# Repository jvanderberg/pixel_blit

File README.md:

# pixel_blit

A 32-channel addressable LED controller based on the Raspberry Pi RP2350B microcontroller.

<details>
<summary>Top view</summary>

</details>

> **Status:** the images show v4.0. This branch (`v5`) is the next revision:
> Wi-Fi instead of LVDS, four independent 5-24 V power zones, a new power
> supply and an on-board status LED and button. It is designed but not yet
> built; bring-up and firmware come after prototyping the RM2 module and
> receiving boards. Design notes, part choices and as-built values are in
> [docs/next-revision.md](docs/next-revision.md).

## Overview

The pixel_blit drives up to 32 strings of addressable LEDs from one board. The
outputs are split into four power zones, each with its own supply input, so
5 V, 12 V and 24 V pixels can run from the same controller. Shows play from a
microSD card; the board is set up and controlled over Wi-Fi, USB or an IR
remote.

## Key Specifications

- **Microcontroller**: Raspberry Pi RP2350B (QFN-80)
  - Dual Cortex-M33 cores @ 150 MHz
  - 12 PIO state machines for LED timing
  - USB Full Speed (12 Mbps)

- **Output Channels**: 32 independent LED string outputs
  - 3.3 V to 5 V level shifting (4× SN74LVC8T245)
  - 47 Ω series resistor on every data line
  - 3 A / 30 V resettable fuse (PTC) on every port
  - Screw terminals (3.5 mm pitch): power, data, ground

- **Power Zones**: 4 zones of 8 outputs each
  - One input per zone, **5-24 V DC**
  - 20 A blade fuse, reverse-polarity ideal diode (LM74700 + 60 V FET) and 26 V TVS on each input
  - A blown-fuse LED beside each fuse
  - Silkscreen key with a write-in voltage box per zone

- **Memory**:
  - 16 MB QSPI flash (W25Q128JV)
  - 8 MB QSPI PSRAM (APS6404L), on the flash bus
  - microSD card slot for shows and settings

- **Wireless**: Raspberry Pi RM2 module (CYW43439, 2.4 GHz Wi-Fi and Bluetooth)

- **User Interface**:
  - Common-cathode RGB status LED
  - Play button, plus Boot and Reset buttons
  - IR receiver jack with a polarity switch
  - USB-C

## Power

```
Zone inputs 1-4 (5-24 V each)
  → 20 A blade fuse → LM74700 ideal diode (blocks a reversed supply) → zone rail VZ1-VZ4
       (SMBJ26A TVS on the rail) → 8 ports, each through a 3 A PTC
  → SS34 diodes (OR of all four zones) → VIN_SYS
       → TPS552872 buck-boost (4.5-28 V in) → 5.2 V → B5819W → +5 V (level shifters)
       → TPS62A02A buck → 3.3 V (MCU, flash, PSRAM, Wi-Fi, SD)
       → RP2350B internal regulator → 1.1 V core
```

The logic supply runs from whichever zones are powered, so any one input is
enough to run the board. USB can power the logic alone. A 4-pin header (3.3 V,
5 V, VIN, GND) allows external supplies; see the notes on the schematic before
using it.

## Signal Path

```
RP2350B GPIO (3.3 V)
  → SN74LVC8T245 level shifter (4× 8-channel)
  → 47 Ω series resistor
  → screw terminal
  → LED string
```

24 V pixels still take 5 V logic data.

## Pin Map

| GPIO | Function |
|---|---|
| 0-31 | LED strings (firmware maps string numbers to GPIOs) |
| 32-35 | RM2 Wi-Fi (power, chip select, data, clock) |
| 36-39 | microSD (SPI) |
| 40 | Play button (to GND, internal pull-up) |
| 41, 43, 45 | Status LED blue, red, green |
| 42 | IR receiver |
| 44, 46 | Spare |
| 47 | PSRAM chip select (XIP_CS1) |

Strings are numbered by zone on the silkscreen: zone 1 is S0-S7, zone 2 S8-S15,
zone 3 S16-S23, zone 4 S24-S31.

## Board Details

- **PCB size**: 197.5 mm × 122.1 mm
- **Layers**: 4 (signal / GND / GND with a local 3.3 V area / signal and GND)
- **Assembly**: all parts on the top side
- **Connectors**:
  - 32× DB301V 3.5 mm screw terminals (LED outputs)
  - 4× DBT50G 9.5 mm screw terminals (zone power inputs)
  - 4× XF-507P blade fuse holders
  - USB-C, microSD, IR jack, SWD header, power override header

## Component Summary

| Type | Count | Notes |
|------|-------|-------|
| Resistors | 67 | 47 Ω series resistors, regulator feedback, LED resistors |
| Capacitors | 61 | Decoupling, regulator input and output, ideal-diode charge pumps |
| Fuses | 36 | 32 port PTCs, 4 blade fuse holders |
| ICs and modules | 14 | MCU, flash, PSRAM, RM2, 4 level shifters, 2 regulators, 4 ideal-diode controllers |
| MOSFETs | 4 | BSC014N06NS, one per zone input (ideal diode) |
| Diodes and LEDs | 52 | 32 data-line TVS, zone TVS, OR diodes, IR clamp, USB protection, status and fuse LEDs |
| Terminal blocks | 36 | 32 LED outputs, 4 zone inputs |
| Buttons and switches | 4 | Play, Boot, Reset, IR polarity |

## File Structure

```
pixel_blit/
├── pixel_blit.kicad_pcb      # PCB layout
├── pixel_blit.kicad_sch      # Top-level schematic: MCU, flash, PSRAM, USB, status LED, buttons
├── Power.kicad_sch           # Zone inputs and ideal diodes, buck-boost, 3.3 V buck, fuse LEDs
├── output.kicad_sch          # Level shifters, series resistors, PTCs, terminals
├── wireless.kicad_sch        # RM2 Wi-Fi module
├── peripherals.kicad_sch     # microSD, IR receiver
├── PixelBlit.kicad_sym/.pretty, JLCImport.kicad_sym/.pretty  # Project libraries
├── docs/                     # Design notes (next-revision.md) and images
└── production/               # Manufacturing outputs
```

## Use Cases

- Architectural lighting installations
- Stage and entertainment lighting
- Large-scale pixel displays
- Holiday and decorative lighting
- Interactive art installations

## License

MIT License

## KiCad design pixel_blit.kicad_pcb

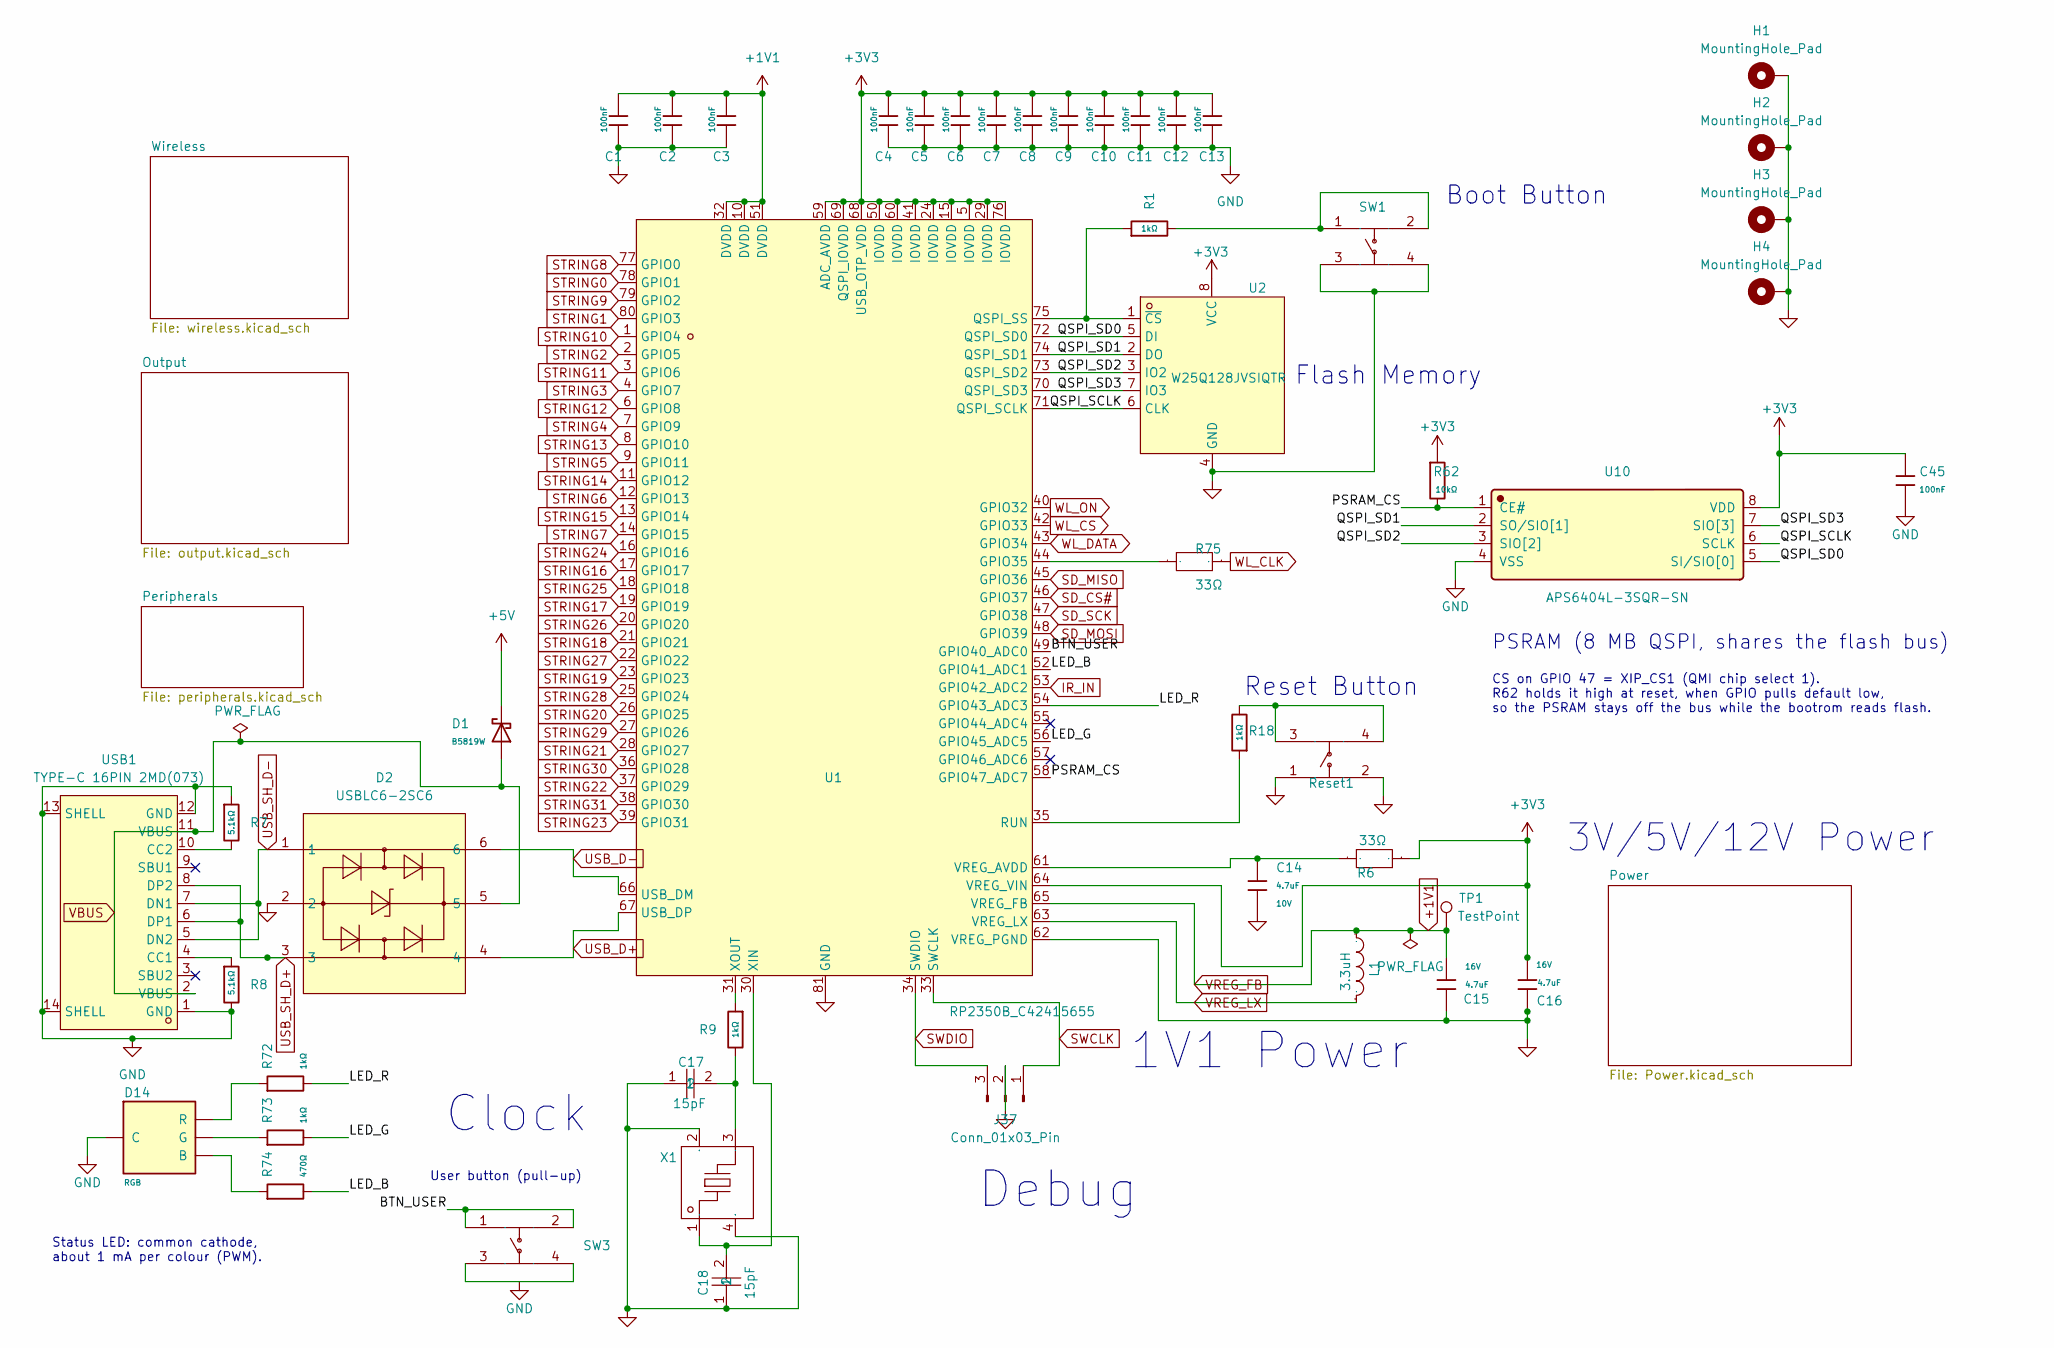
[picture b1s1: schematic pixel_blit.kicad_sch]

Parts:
C1, C2, C3, C4, C5, C6, C7, C8, C9, C10, C11, C12, C13, C45: 100nF; C_0402; Voltage Rated 16V; Tolerance ±10%; Part CL05B104KO5NNNC; LCSC C1525
C14: 4.7uF; C_0402; Voltage Rated 10V; Tolerance ±20%; Part CL05A475MP5NRNC; LCSC C23733
C15, C16: 4.7uF; C_0603; Voltage Rated 16V; Tolerance ±10%; Part CL10A475KO8NNNC; LCSC C19666
C17, C18: 15pF; C0402; Manufacturer Part 0402CG150J500NT; LCSC Part Name 15pF ±5% 50V
D1: B5819W; D_SOD-123; Forward Voltage (Vf@If) 900mV@3A; Reverse Voltage (Vr) 40V; Part B5819W; LCSC C64885
D2: USBLC6-2SC6; SOT-23-6_L2.9-W1.6-P0.95-LS2.8-BL; LCSC Part C7519
D14: RGB; TJ-S1615CY6TGLCCSRGB-A5; Manufacturer Part TJ-S1615CY6TGLCCSRGB-A5; LCSC C601684
H1, H2, H3, H4: MountingHole_Pad; MountingHole_3.2mm_M3_Pad_Via
J37: Conn_01x03_Pin; PinHeader_1x03_P2.54mm_Vertical
L1: IND-SMD_L2.0-W1.6_AOTA-B201610S3R3-101-T; Manufacturer Part AOTA-B201610S3R3-101-T; LCSC Part Name AOTA-B201610S3R3-101-T
R1, R18, R72, R73: 1kΩ; R_0402; Overload Voltage (Max) 50V; Tolerance ±1%; Part 0402WGF1001TCE; LCSC C11702
R6, R75: 33Ω; R0402; Manufacturer Part 0402WGF330JTCE; LCSC Part Name 33Ω ±1% 62.5mW 厚膜电阻
R7, R8: 5.1kΩ; R_0402; Overload Voltage (Max) 50V; Tolerance ±1%; Part 0402WGF5101TCE; LCSC C25905
R9: 1kΩ; R_0603; Overload Voltage (Max) 75V; Tolerance ±1%; Part 0603WAF1001T5E; LCSC C21190
R62: 10kΩ; R_0402; Overload Voltage (Max) 50V; Tolerance ±1%; Part 0402WGF1002TCE; LCSC C25744
R74: 470Ω; R_0402; Overload Voltage (Max) 50V; Tolerance ±1%; Part 0402WGF4700TCE; LCSC C25117
Reset1: K2-1808SN-A4SW-01; KEY-SMD_4P-L4.2-W3.2-P2.20-LS5.1-TL; Manufacturer Part K2-1808SN-A4SW-01; LCSC Part Name 4.2mm*3.25mm
SW1: K2-1808SN-A4SW; KEY-SMD_4P-L4.2-W3.2-P2.20-LS5.1-TL; LCSC Part C92589
SW3: KEY-SMD_4P-L4.2-W3.2-P2.20-LS5.1-TL; Manufacturer Part K2-1808SN-A4SW-01; LCSC Part Name 4.2mm*3.25mm
TP1: TestPoint; TestPoint_Pad_1.0x1.0mm
U1: RP2350B_C42415655; QFN-80_L10.0-W10.0-P0.40-TL-EP3.4; LCSC Part C42415655
U2: W25Q128JVSIQTR; SOIC-8_L5.3-W5.3-P1.27-LS8.0-BL; LCSC Part C97521
U10: APS6404L-3SQR-SN; APS6404L-3SQR-SN_C5333729; Manufacturer Part APS6404L-3SQR-SN; LCSC C5333729
USB1: TYPE-C 16PIN 2MD(073); USB-C-SMD_TYPE-C-6PIN-2MD-073; LCSC Part C2765186
X1: CRYSTAL-SMD_4P-L3.2-W2.5-BL; Manufacturer Part ABM8-272-T3; LCSC Part Name ABM8-272-T3

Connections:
+1V1: C1.1, C2.1, C3.1, C15.2, L1.2, TP1.1, U1.10 (DVDD), U1.32 (DVDD), U1.51 (DVDD), U1.65 (VREG_FB)
+3V3: C4.1, C5.1, C6.1, C7.1, C8.1, C9.1, C10.1, C11.1, C12.1, C13.1, C16.2, C45.1, R6.1, R62.1, U1.5 (IOVDD), U1.15 (IOVDD), U1.24 (IOVDD), U1.29 (IOVDD), U1.41 (IOVDD), U1.50 (IOVDD), U1.59 (ADC_AVDD), U1.60 (IOVDD), U1.64 (VREG_VIN), U1.68 (USB_OTP_VDD), U1.69 (QSPI_IOVDD), U1.76 (IOVDD), U2.8 (VCC), U10.8 (VDD); also elsewhere on the board
+5V: D1.1; also elsewhere on the board
/BTN_USER: SW3.1, SW3.2, U1.49 (GPIO40_ADC0)
/LED_B: R74.2, U1.52 (GPIO41_ADC1)
/LED_G: R73.2, U1.56 (GPIO45_ADC5)
/LED_R: R72.2, U1.54 (GPIO43_ADC3)
/PSRAM_CS: R62.2, U1.58 (GPIO47_ADC7), U10.1 (CE#)
/QSPI_SCLK: U1.71 (QSPI_SCLK), U2.6 (CLK), U10.6 (SCLK)
/QSPI_SD0: U1.72 (QSPI_SD0), U2.5 (DI), U10.5 (SI/SIO[0])
/QSPI_SD1: U1.74 (QSPI_SD1), U2.2 (DO), U10.2 (SO/SIO[1])
/QSPI_SD2: U1.73 (QSPI_SD2), U2.3 (IO2), U10.3 (SIO[2])
/QSPI_SD3: U1.70 (QSPI_SD3), U2.7 (IO3), U10.7 (SIO[3])
GND: C1.2, C2.2, C3.2, C4.2, C5.2, C6.2, C7.2, C8.2, C9.2, C10.2, C11.2, C12.2, C13.2, C14.2, C15.1, C16.1, C17.1, C18.1, C45.2, D2.2, D14.1 (C), H1.1, H2.1, H3.1, H4.1, J37.2, R7.1, R8.2, Reset1.1, Reset1.2, SW1.3, SW1.4, SW3.3, SW3.4, U1.62 (VREG_PGND), U1.81 (GND), U2.4 (GND), U10.4 (VSS), USB1.1 (GND), USB1.12 (GND), USB1.13 (SHELL), USB1.14 (SHELL), X1.2 (GND), X1.4 (GND); also elsewhere on the board
IR_IN: U1.53 (GPIO42_ADC2); also elsewhere on the board
unnamed: C17.2, R9.2, X1.3
unnamed: D14.2 (B), R74.1
unnamed: D14.3 (G), R73.1
unnamed: D14.4 (R), R72.1
unnamed: R1.2, SW1.1, SW1.2
unnamed: R18.2, Reset1.3, Reset1.4
unnamed: R75.2, U1.44 (GPIO35)
unnamed: R1.1, U1.75 (QSPI_SS), U2.1 (~CS)
unnamed: R18.1, U1.35 (RUN)
unnamed: C14.1, R6.2, U1.61 (VREG_AVDD)
unnamed: C18.2, U1.30 (XIN), X1.1
unnamed: R9.1, U1.31 (XOUT)
unnamed: R8.1, USB1.4 (CC1)
unnamed: R7.2, USB1.10 (CC2)
SD_CS#: U1.46 (GPIO37); also elsewhere on the board
SD_MISO: U1.45 (GPIO36); also elsewhere on the board
SD_MOSI: U1.48 (GPIO39); also elsewhere on the board
SD_SCK: U1.47 (GPIO38); also elsewhere on the board
STRING0: U1.78 (GPIO1); also elsewhere on the board
STRING1: U1.80 (GPIO3); also elsewhere on the board
STRING2: U1.2 (GPIO5); also elsewhere on the board
STRING3: U1.4 (GPIO7); also elsewhere on the board
STRING4: U1.7 (GPIO9); also elsewhere on the board
STRING5: U1.9 (GPIO11); also elsewhere on the board
STRING6: U1.12 (GPIO13); also elsewhere on the board
STRING7: U1.14 (GPIO15); also elsewhere on the board
STRING8: U1.77 (GPIO0); also elsewhere on the board
STRING9: U1.79 (GPIO2); also elsewhere on the board
STRING10: U1.1 (GPIO4); also elsewhere on the board
STRING11: U1.3 (GPIO6); also elsewhere on the board
STRING12: U1.6 (GPIO8); also elsewhere on the board
STRING13: U1.8 (GPIO10); also elsewhere on the board
STRING14: U1.11 (GPIO12); also elsewhere on the board
STRING15: U1.13 (GPIO14); also elsewhere on the board
STRING16: U1.17 (GPIO17); also elsewhere on the board
STRING17: U1.19 (GPIO19); also elsewhere on the board
STRING18: U1.21 (GPIO21); also elsewhere on the board
STRING19: U1.23 (GPIO23); also elsewhere on the board
STRING20: U1.26 (GPIO25); also elsewhere on the board
STRING21: U1.28 (GPIO27); also elsewhere on the board
STRING22: U1.37 (GPIO29); also elsewhere on the board
STRING23: U1.39 (GPIO31); also elsewhere on the board
STRING24: U1.16 (GPIO16); also elsewhere on the board
STRING25: U1.18 (GPIO18); also elsewhere on the board
STRING26: U1.20 (GPIO20); also elsewhere on the board
STRING27: U1.22 (GPIO22); also elsewhere on the board
STRING28: U1.25 (GPIO24); also elsewhere on the board
STRING29: U1.27 (GPIO26); also elsewhere on the board
STRING30: U1.36 (GPIO28); also elsewhere on the board
STRING31: U1.38 (GPIO30); also elsewhere on the board
SWCLK: J37.1, U1.33 (SWCLK)
SWDIO: J37.3, U1.34 (SWDIO)
USB_D+: D2.4, U1.67 (USB_DP)
USB_D-: D2.6, U1.66 (USB_DM)
USB_SH_D+: D2.3, USB1.6 (DP1), USB1.8 (DP2)
USB_SH_D-: D2.1, USB1.5 (DN2), USB1.7 (DN1)
VBUS: D1.2, D2.5, USB1.2 (VBUS), USB1.11 (VBUS)
VREG_LX: L1.1, U1.63 (VREG_LX)
WL_CLK: R75.1; also elsewhere on the board
WL_CS: U1.42 (GPIO33); also elsewhere on the board
WL_DATA: U1.43 (GPIO34); also elsewhere on the board
WL_ON: U1.40 (GPIO32); also elsewhere on the board

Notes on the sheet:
Reset Button
Debug
Status LED: common cathode, about 1 mA per colour (PWM).
Boot Button
Clock
CS on GPIO 47 = XIP_CS1 (QMI chip select 1). R62 holds it high at reset, when GPIO pulls default low, so the PSRAM stays off the bus while the bootrom reads flash.
3V/5V/12V Power
Flash Memory
PSRAM (8 MB QSPI, shares the flash bus)
User button (pull-up)
1V1 Power

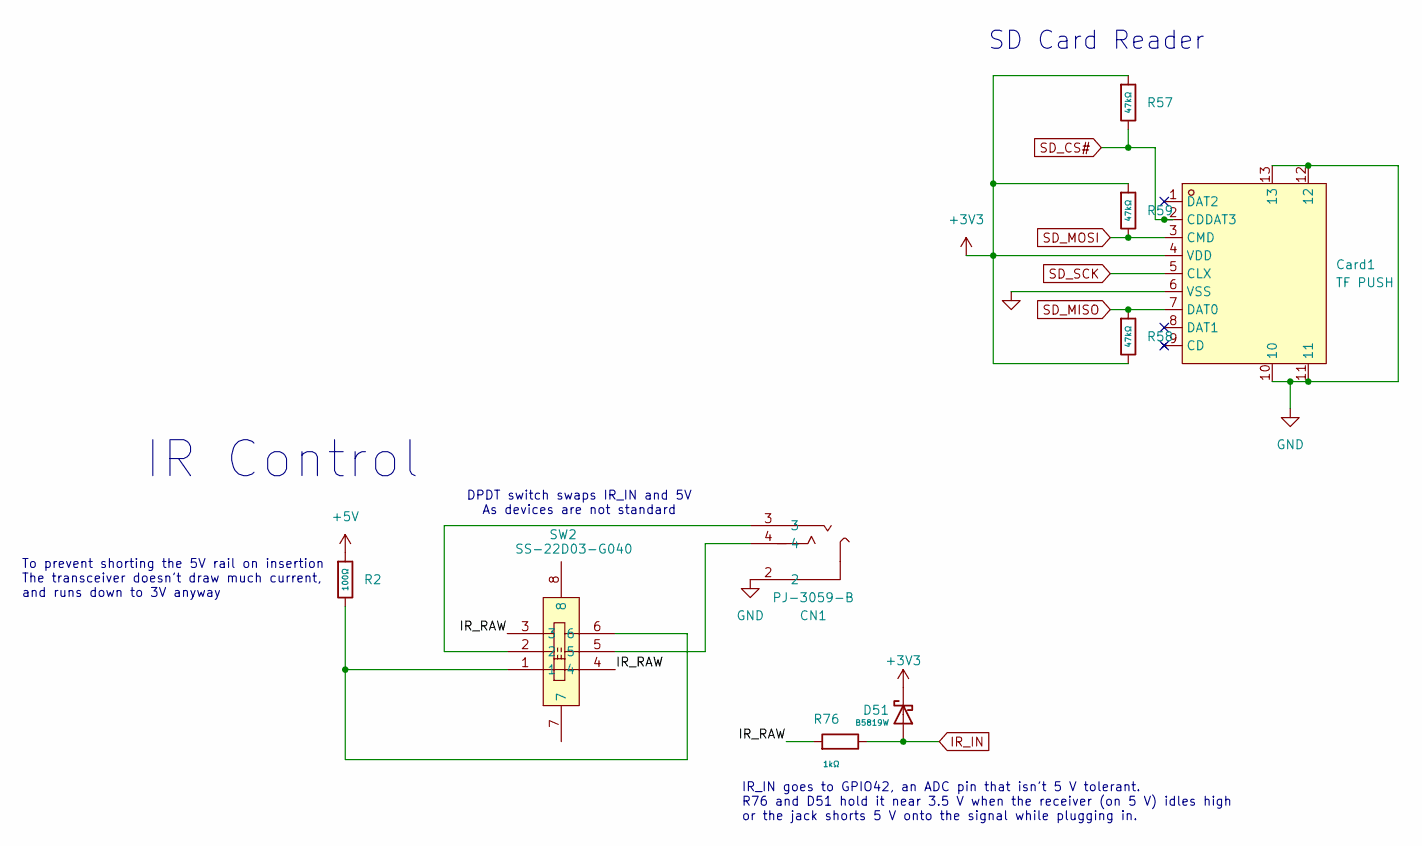
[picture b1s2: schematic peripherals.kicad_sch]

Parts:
CN1: PJ-3059-B; AUDIO-TH_XKB_PJ-3059-B; LCSC Part C2884976
Card1: TF PUSH; TF-SMD_TF-PUSH; LCSC Part C393941
D51: B5819W; D_SOD-123; Forward Voltage (Vf@If) 900mV@3A; Reverse Voltage (Vr) 40V; Part B5819W; LCSC C64885
R2: 100Ω; R_0603; Overload Voltage (Max) 75V; Tolerance ±1%; Part 0603WAF1000T5E; LCSC C22775
R57, R58, R59: 47kΩ; R_0402; Overload Voltage (Max) 50V; Tolerance ±1%; Part 0402WGF4702TCE; LCSC C25792
R76: 1kΩ; R_0402; Overload Voltage (Max) 50V; Tolerance ±1%; Part 0402WGF1001TCE; LCSC C11702
SW2: SS-22D03-G040; SW-TH_SS-22D03-G4; LCSC Part C2848923

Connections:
+3V3: Card1.4 (VDD), D51.1, R57.1, R58.2, R59.1; also elsewhere on the board
+5V: R2.1; also elsewhere on the board
/Peripherals/IR_RAW: R76.1, SW2.3, SW2.4
GND: CN1.2, Card1.6 (VSS), Card1.10, Card1.11, Card1.12, Card1.13; also elsewhere on the board
IR_IN: D51.2, R76.2; also elsewhere on the board
unnamed: CN1.3, SW2.2
unnamed: CN1.4, SW2.5
unnamed: R2.2, SW2.1, SW2.6
SD_CS#: Card1.2 (CDDAT3), R57.2; also elsewhere on the board
SD_MISO: Card1.7 (DAT0), R58.1; also elsewhere on the board
SD_MOSI: Card1.3 (CMD), R59.2; also elsewhere on the board
SD_SCK: Card1.5 (CLX); also elsewhere on the board

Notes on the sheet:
IR Control
SD Card Reader
DPDT switch swaps IR_IN and 5V As devices are not standard
To prevent shorting the 5V rail on insertion The transceiver doesn't draw much current, and runs down to 3V anyway
IR_IN goes to GPIO42, an ADC pin that isn't 5 V tolerant. R76 and D51 hold it near 3.5 V when the receiver (on 5 V) idles high or the jack shorts 5 V onto the signal while plugging in.

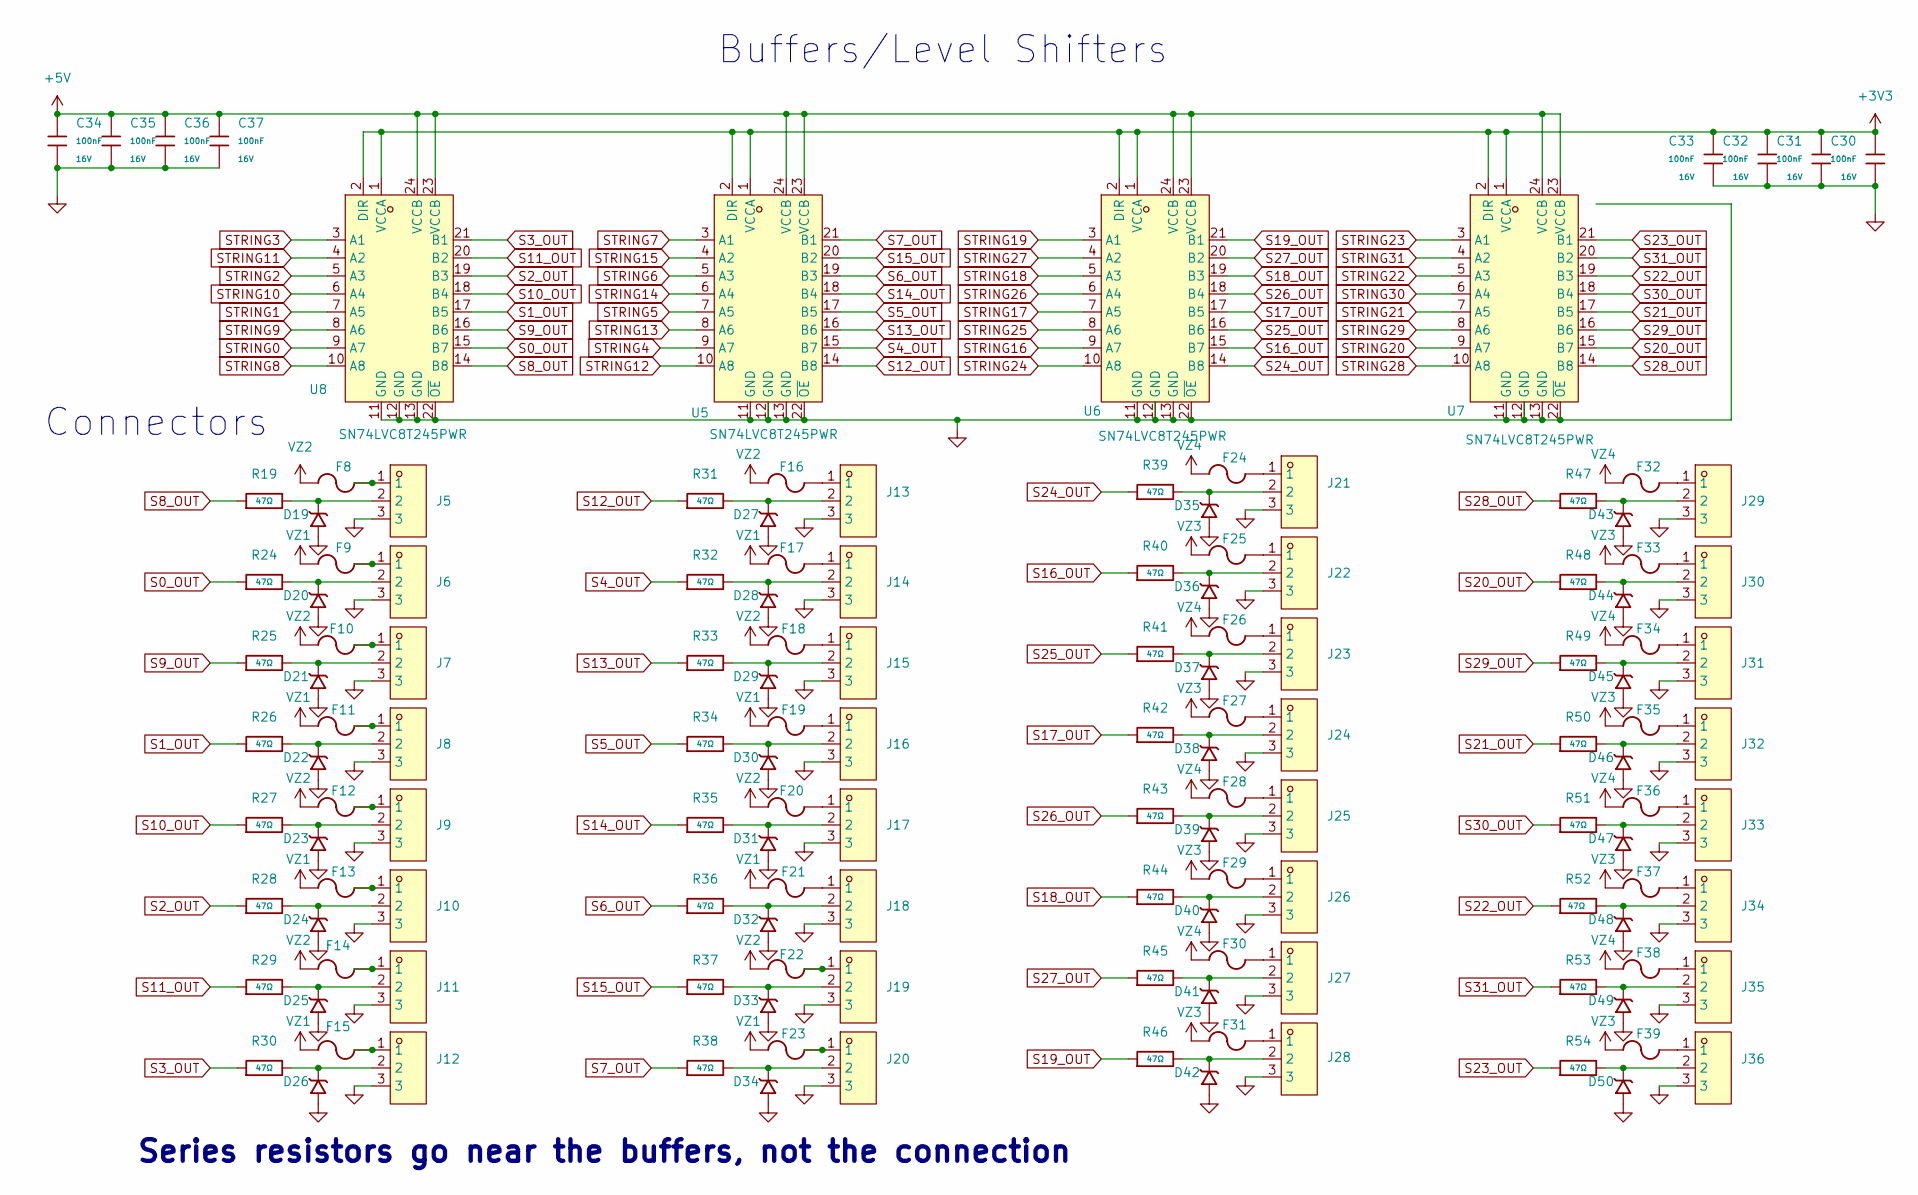
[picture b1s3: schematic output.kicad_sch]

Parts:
C30, C31, C32, C33, C34, C35, C36, C37: 100nF; C_0402; Voltage Rated 16V; Tolerance ±10%; Part CL05B104KO5NNNC; LCSC C1525
D19, D20, D21, D22, D23, D24, D25, D26, D27, D28, D29, D30, D31, D32, D33, D34, D35, D36, D37, D38, D39, D40, D41, D42, D43, D44, D45, D46, D47, D48, D49, D50: SMF5.0A; SMF5_0A_C193402; Manufacturer Part SMF5.0A; LCSC C193402
F8, F9, F10, F11, F12, F13, F14, F15, F16, F17, F18, F19, F20, F21, F22, F23, F24, F25, F26, F27, F28, F29, F30, F31, F32, F33, F34, F35, F36, F37, F38, F39: 1812L300/30GR; 1812L300_30GR; Manufacturer Part 1812L300/30GR; LCSC C48985875
J5, J6, J7, J8, J9, J10, J11, J12, J13, J14, J15, J16, J17, J18, J19, J20, J21, J22, J23, J24, J25, J26, J27, J28, J29, J30, J31, J32, J33, J34, J35, J36: DB301V-3.5-3P-GN; CONN-TH_DB301V-3.5-3P-GN; LCSC Part C695630
R19, R24, R25, R26, R27, R28, R29, R30, R31, R32, R33, R34, R35, R36, R37, R38, R39, R40, R41, R42, R43, R44, R45, R46, R47, R48, R49, R50, R51, R52, R53, R54: 47Ω; R_0402; Overload Voltage (Max) 50V; Tolerance ±1%; Part 0402WGF470JTCE; LCSC C25118
U5, U6, U7, U8: SN74LVC8T245PWR; TSSOP-24_L7.8-W4.4-P0.65-LS6.4-BL; LCSC Part C27643

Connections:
+3V3: C30.1, C31.1, C32.1, C33.1, U5.1 (VCCA), U5.2 (DIR), U6.1 (VCCA), U6.2 (DIR), U7.1 (VCCA), U7.2 (DIR), U8.1 (VCCA), U8.2 (DIR); also elsewhere on the board
+5V: C34.1, C35.1, C36.1, C37.1, U5.23 (VCCB), U5.24 (VCCB), U6.23 (VCCB), U6.24 (VCCB), U7.23 (VCCB), U7.24 (VCCB), U8.23 (VCCB), U8.24 (VCCB); also elsewhere on the board
GND: C30.2, C31.2, C32.2, C33.2, C34.2, C35.2, C36.2, C37.2, D19.2 (A), D20.2 (A), D21.2 (A), D22.2 (A), D23.2 (A), D24.2 (A), D25.2 (A), D26.2 (A), D27.2 (A), D28.2 (A), D29.2 (A), D30.2 (A), D31.2 (A), D32.2 (A), D33.2 (A), D34.2 (A), D35.2 (A), D36.2 (A), D37.2 (A), D38.2 (A), D39.2 (A), D40.2 (A), D41.2 (A), D42.2 (A), D43.2 (A), D44.2 (A), D45.2 (A), D46.2 (A), D47.2 (A), D48.2 (A), D49.2 (A), D50.2 (A), J5.3, J6.3, J7.3, J8.3, J9.3, J10.3, J11.3, J12.3, J13.3, J14.3, J15.3, J16.3, J17.3, J18.3, J19.3, J20.3, J21.3, J22.3, J23.3, J24.3, J25.3, J26.3, J27.3, J28.3, J29.3, J30.3, J31.3, J32.3, J33.3, J34.3, J35.3, J36.3, U5.11 (GND), U5.12 (GND), U5.13 (GND), U5.22 (~OE), U6.11 (GND), U6.12 (GND), U6.13 (GND), U6.22 (~OE), U7.11 (GND), U7.12 (GND), U7.13 (GND), U7.22 (~OE), U8.11 (GND), U8.12 (GND), U8.13 (GND), U8.22 (~OE); also elsewhere on the board
unnamed: D19.1 (C), J5.2, R19.2
unnamed: D20.1 (C), J6.2, R24.2
unnamed: D21.1 (C), J7.2, R25.2
unnamed: D22.1 (C), J8.2, R26.2
unnamed: D23.1 (C), J9.2, R27.2
unnamed: D24.1 (C), J10.2, R28.2
unnamed: D25.1 (C), J11.2, R29.2
unnamed: D26.1 (C), J12.2, R30.2
unnamed: D27.1 (C), J13.2, R31.2
unnamed: D28.1 (C), J14.2, R32.2
unnamed: D29.1 (C), J15.2, R33.2
unnamed: D30.1 (C), J16.2, R34.2
unnamed: D31.1 (C), J17.2, R35.2
unnamed: D32.1 (C), J18.2, R36.2
unnamed: D33.1 (C), J19.2, R37.2
unnamed: D34.1 (C), J20.2, R38.2
unnamed: D35.1 (C), J21.2, R39.2
unnamed: D36.1 (C), J22.2, R40.2
unnamed: D37.1 (C), J23.2, R41.2
unnamed: D38.1 (C), J24.2, R42.2
unnamed: D39.1 (C), J25.2, R43.2
unnamed: D40.1 (C), J26.2, R44.2
unnamed: D41.1 (C), J27.2, R45.2
unnamed: D42.1 (C), J28.2, R46.2
unnamed: D43.1 (C), J29.2, R47.2
unnamed: D44.1 (C), J30.2, R48.2
unnamed: D45.1 (C), J31.2, R49.2
unnamed: D46.1 (C), J32.2, R50.2
unnamed: D47.1 (C), J33.2, R51.2
unnamed: D48.1 (C), J34.2, R52.2
unnamed: D49.1 (C), J35.2, R53.2
unnamed: D50.1 (C), J36.2, R54.2
unnamed: F8.2, J5.1
unnamed: F9.2, J6.1
unnamed: F10.2, J7.1
unnamed: F11.2, J8.1
unnamed: F12.2, J9.1
unnamed: F13.2, J10.1
unnamed: F14.2, J11.1
unnamed: F15.2, J12.1
unnamed: F16.2, J13.1
unnamed: F17.2, J14.1
unnamed: F18.2, J15.1
unnamed: F19.2, J16.1
unnamed: F20.2, J17.1
unnamed: F21.2, J18.1
unnamed: F22.2, J19.1
unnamed: F23.2, J20.1
unnamed: F24.2, J21.1
unnamed: F25.2, J22.1
unnamed: F26.2, J23.1
unnamed: F27.2, J24.1
unnamed: F28.2, J25.1
unnamed: F29.2, J26.1
unnamed: F30.2, J27.1
unnamed: F31.2, J28.1
unnamed: F32.2, J29.1
unnamed: F33.2, J30.1
unnamed: F34.2, J31.1
unnamed: F35.2, J32.1
unnamed: F36.2, J33.1
unnamed: F37.2, J34.1
unnamed: F38.2, J35.1
unnamed: F39.2, J36.1
S0_OUT: R24.1, U8.15 (B7)
S1_OUT: R26.1, U8.17 (B5)
S2_OUT: R28.1, U8.19 (B3)
S3_OUT: R30.1, U8.21 (B1)
S4_OUT: R32.1, U5.15 (B7)
S5_OUT: R34.1, U5.17 (B5)
S6_OUT: R36.1, U5.19 (B3)
S7_OUT: R38.1, U5.21 (B1)
S8_OUT: R19.1, U8.14 (B8)
S9_OUT: R25.1, U8.16 (B6)
S10_OUT: R27.1, U8.18 (B4)
S11_OUT: R29.1, U8.20 (B2)
S12_OUT: R31.1, U5.14 (B8)
S13_OUT: R33.1, U5.16 (B6)
S14_OUT: R35.1, U5.18 (B4)
S15_OUT: R37.1, U5.20 (B2)
S16_OUT: R40.1, U6.15 (B7)
S17_OUT: R42.1, U6.17 (B5)
S18_OUT: R44.1, U6.19 (B3)
S19_OUT: R46.1, U6.21 (B1)
S20_OUT: R48.1, U7.15 (B7)
S21_OUT: R50.1, U7.17 (B5)
S22_OUT: R52.1, U7.19 (B3)
S23_OUT: R54.1, U7.21 (B1)
S24_OUT: R39.1, U6.14 (B8)
S25_OUT: R41.1, U6.16 (B6)
S26_OUT: R43.1, U6.18 (B4)
S27_OUT: R45.1, U6.20 (B2)
S28_OUT: R47.1, U7.14 (B8)
S29_OUT: R49.1, U7.16 (B6)
S30_OUT: R51.1, U7.18 (B4)
S31_OUT: R53.1, U7.20 (B2)
STRING0: U8.9 (A7); also elsewhere on the board
STRING1: U8.7 (A5); also elsewhere on the board
STRING2: U8.5 (A3); also elsewhere on the board
STRING3: U8.3 (A1); also elsewhere on the board
STRING4: U5.9 (A7); also elsewhere on the board
STRING5: U5.7 (A5); also elsewhere on the board
STRING6: U5.5 (A3); also elsewhere on the board
STRING7: U5.3 (A1); also elsewhere on the board
STRING8: U8.10 (A8); also elsewhere on the board
STRING9: U8.8 (A6); also elsewhere on the board
STRING10: U8.6 (A4); also elsewhere on the board
STRING11: U8.4 (A2); also elsewhere on the board
STRING12: U5.10 (A8); also elsewhere on the board
STRING13: U5.8 (A6); also elsewhere on the board
STRING14: U5.6 (A4); also elsewhere on the board
STRING15: U5.4 (A2); also elsewhere on the board
STRING16: U6.9 (A7); also elsewhere on the board
STRING17: U6.7 (A5); also elsewhere on the board
STRING18: U6.5 (A3); also elsewhere on the board
STRING19: U6.3 (A1); also elsewhere on the board
STRING20: U7.9 (A7); also elsewhere on the board
STRING21: U7.7 (A5); also elsewhere on the board
STRING22: U7.5 (A3); also elsewhere on the board
STRING23: U7.3 (A1); also elsewhere on the board
STRING24: U6.10 (A8); also elsewhere on the board
STRING25: U6.8 (A6); also elsewhere on the board
STRING26: U6.6 (A4); also elsewhere on the board
STRING27: U6.4 (A2); also elsewhere on the board
STRING28: U7.10 (A8); also elsewhere on the board
STRING29: U7.8 (A6); also elsewhere on the board
STRING30: U7.6 (A4); also elsewhere on the board
STRING31: U7.4 (A2); also elsewhere on the board
VZ1: F9.1, F11.1, F13.1, F15.1, F17.1, F19.1, F21.1, F23.1; also elsewhere on the board
VZ2: F8.1, F10.1, F12.1, F14.1, F16.1, F18.1, F20.1, F22.1; also elsewhere on the board
VZ3: F25.1, F27.1, F29.1, F31.1, F33.1, F35.1, F37.1, F39.1; also elsewhere on the board
VZ4: F24.1, F26.1, F28.1, F30.1, F32.1, F34.1, F36.1, F38.1; also elsewhere on the board

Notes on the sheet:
Buffers/Level Shifters
Connectors
Series resistors go near the buffers, not the connection
